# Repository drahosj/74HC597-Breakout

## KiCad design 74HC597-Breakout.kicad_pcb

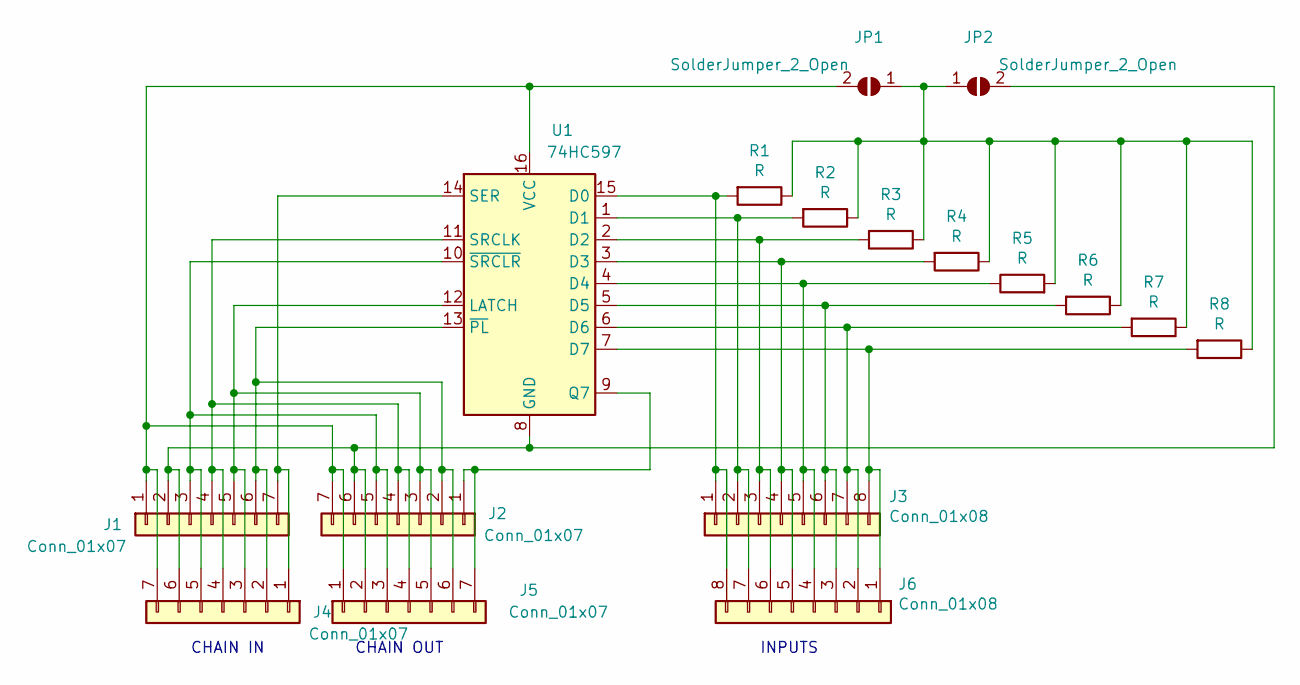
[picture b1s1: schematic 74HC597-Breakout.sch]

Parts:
J1, J2: Conn_01x07; Conn_Pads_7
J3: Conn_01x08; Conn_Pads_8
J4, J5: Conn_01x07; Molex_PicoBlade_53261-0771_1x07-1MP_P1.25mm_Horizontal
J6: Conn_01x08; Molex_PicoBlade_53261-0871_1x08-1MP_P1.25mm_Horizontal
JP1, JP2: SolderJumper_2_Open; SolderJumper-2_P1.3mm_Open_TrianglePad1.0x1.5mm
R1, R2, R3, R4, R5, R6, R7, R8: R; R_0805_2012Metric
U1: 74HC597; SOIC-16_3.9x9.9mm_P1.27mm

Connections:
unnamed: J1.1, J2.7, J4.7, J5.1, JP1.2 (B), U1.16 (VCC)
unnamed: J1.2, J2.6, J4.6, J5.2, JP2.2 (B), U1.8 (GND)
unnamed: J1.3, J2.5, J4.5, J5.3, U1.10 (~SRCLR)
unnamed: J1.4, J2.4, J4.4, J5.4, U1.11 (SRCLK)
unnamed: J1.5, J2.3, J4.3, J5.5, U1.12 (LATCH)
unnamed: J1.6, J2.2, J4.2, J5.6, U1.13 (~PL)
unnamed: J1.7, J4.1, U1.14 (SER)
unnamed: J2.1, J5.7, U1.9 (Q7)
unnamed: J3.1, J6.8, R1.2, U1.15 (D0)
unnamed: J3.2, J6.7, R2.2, U1.1 (D1)
unnamed: J3.3, J6.6, R3.2, U1.2 (D2)
unnamed: J3.4, J6.5, R4.2, U1.3 (D3)
unnamed: J3.5, J6.4, R5.1, U1.4 (D4)
unnamed: J3.6, J6.3, R6.2, U1.5 (D5)
unnamed: J3.7, J6.2, R7.2, U1.6 (D6)
unnamed: J3.8, J6.1, R8.2, U1.7 (D7)
unnamed: JP1.1 (A), JP2.1 (A), R1.1, R2.1, R3.1, R4.1, R5.2, R6.1, R7.1, R8.1

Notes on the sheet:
INPUTS
CHAIN IN
CHAIN OUT

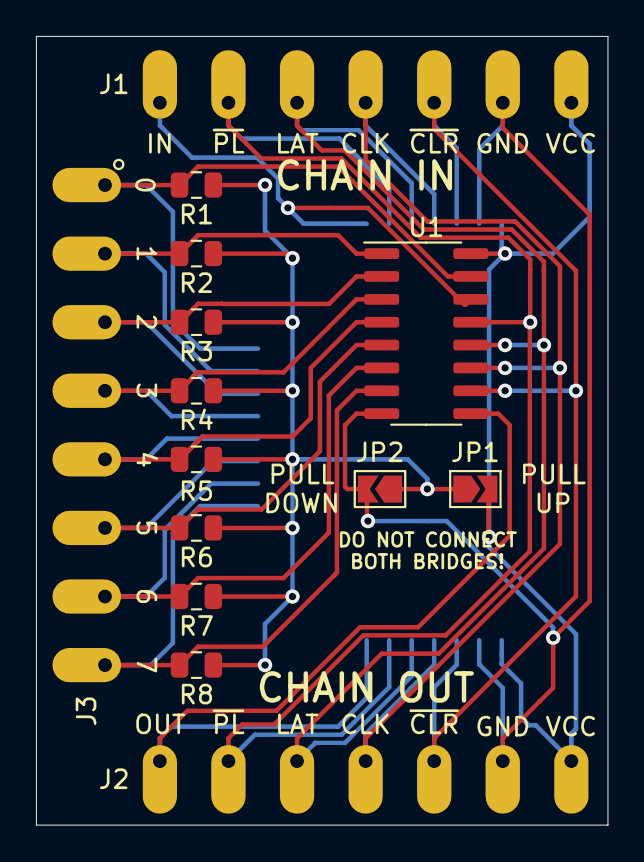
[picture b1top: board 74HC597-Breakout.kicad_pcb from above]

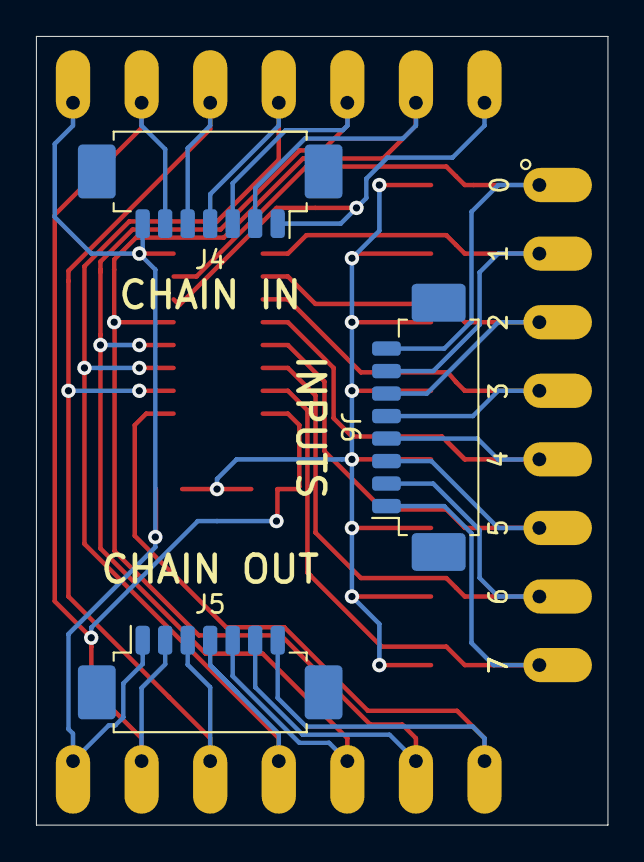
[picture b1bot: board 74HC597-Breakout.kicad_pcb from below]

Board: 2 copper layers, 31.7 x 43.8 mm, 17 parts (3 on the bottom side), 17 nets.

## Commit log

2020-09-03 Done?
2020-09-03 Local symbols into project lib, also plots
    Plotted gerbers and schematic
    Moved symbol into a local library
